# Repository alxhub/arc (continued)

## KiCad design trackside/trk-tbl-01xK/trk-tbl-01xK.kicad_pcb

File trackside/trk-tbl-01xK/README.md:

# ARC-TRK-TBL-01xK

ARC-TRK-TBL-01xK is the trackside controller for a Kato turntable. It connects to an ARC track hub over a LIN cable, moves the bridge, operates its lock, and counts the turntable's index contact as the bridge passes each stop. A homing sensor port can establish an absolute starting position.

The rails on the moving bridge receive power from a separate ARC district. This board passes that pair to the Kato cable and reports whether the feed is active. The controller does not drive the track rails.

An expansion port can host a nearby angle sensor or other I²C accessory.

[Board design](board.kdl)
[PCB layout](trk-tbl-01xK.kicad_pcb)

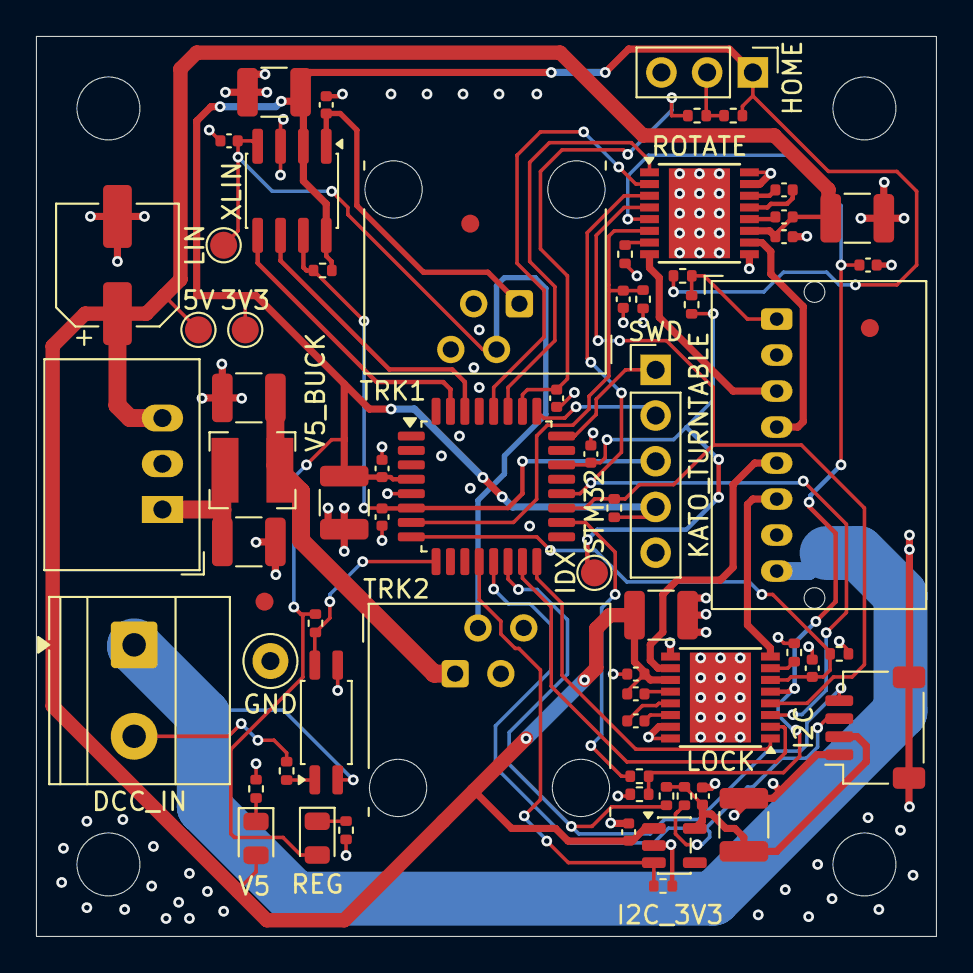
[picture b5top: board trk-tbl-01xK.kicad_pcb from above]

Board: 4 copper layers, 50.0 x 50.0 mm, 73 parts (0 on the bottom side), 48 nets.

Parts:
3V3, 5V: TestPoint; TestPoint_Pad_D1.5mm
C1, C6, C8, C12, C13, C16, C17, C21, C22: 100nF; C_0402_1005Metric
C2, C4, C5, C10, C11, C25: 10µF; C_1210_3225Metric
C3: 220pF; C_0402_1005Metric
C7: 4.7µF; C_1210_3225Metric
C9: 100µF; CP_Elec_6.3x5.8
C14, C15: 22nF; C_0402_1005Metric
C18, C23, C24: 1µF; C_0402_1005Metric
C19, C20: 10nF; C_0402_1005Metric
DCC_IN: Conn_01x02; TerminalBlock_Phoenix_MKDS-1,5-2-5.08_1x02_P5.08mm_Horizont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
FID1, FID2, FID3: Fiducial; Fiducial_1mm_Mask2mm
GND: TestPoint; TestPoint_Loop_D2.50mm_Drill1.0mm
H1, H2, H3, H4: MountingHole; MountingHole_3.5mm
HOME: Conn_01x03; PinHeader_1x03_P2.54mm_Vertical
I2C: Conn_01x04_MountingPin; JST_SH_SM04B-SRSS-TB_1x04-1MP_P1.00mm_Horizontal
I2C_3V3: AP2112K-3.3; SOT-23-5
IDX: TestPoint; TestPoint_Pad_D1.5mm
KATO_TURNTABLE: Conn_01x08; JST_PA_S08B-PASK-2_1x08_P2.00mm_Horizontal
L1: 15µH; L_Bourns-SRN4018
LIN: TestPoint; TestPoint_Pad_D1.5mm
LOCK: DRV8874PWPR; HTSSOP-16-1EP_4.4x5mm_P0.65mm_EP3.4x5mm
R1, R4, R5, R11: 10kΩ; R_0402_1005Metric
R2, R3: 20kΩ; R_0402_1005Metric
R6: 1MΩ; R_0402_1005Metric
R7, R8: 1.21kΩ; R_0402_1005Metric
R9: 2.2kΩ; R_0402_1005Metric
R10, R12: 1kΩ; R_0402_1005Metric
R13: 11kΩ; R_0402_1005Metric
R14, R17: 100kΩ; R_0402_1005Metric
R15: 680Ω; R_0402_1005Metric
R16: 1.5kΩ; R_0402_1005Metric
R18, R19: 4.7kΩ; R_0402_1005Metric
REG: green; LED_0805_2012Metric
ROTATE: DRV8874PWPR; HTSSOP-16-1EP_4.4x5mm_P0.65mm_EP3.4x5mm
STM32: STM32C092KBTx; LQFP-32_7x7mm_P0.8mm
SWD: Conn_01x05; PinHeader_1x05_P2.54mm_Vertical
TRK1, TRK2: RJ11; RJ11_Stewart_SS-90000-006_Horizontal
U1: FODM214; SOP-4_4.4x2.6mm_P1.27mm
V5: green; LED_0805_2012Metric
V5_BUCK: R-78E5.0-1.0; Converter_DCDC_RECOM_R-78E-0.5_THT
XLIN: NCV7428D13R2G; SOIC-8_3.9x4.9mm_P1.27mm

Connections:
unnamed: I2C_3V3.3, R17.1, STM32.12
unnamed: C15.1, LOCK.13
unnamed: C15.2, LOCK.14
unnamed: LOCK.7, R3.1
unnamed: C17.2, LOCK.12
unnamed: R15.1, REG.1
unnamed: C14.1, ROTATE.13
unnamed: C14.2, ROTATE.14
unnamed: R2.1, ROTATE.7
unnamed: C16.2, ROTATE.12
unnamed: R13.2, U1.1
unnamed: R16.1, V5.1
expansion/pulls/i2c.scl: I2C.4, R19.1, STM32.14
expansion/pulls/i2c.sda: I2C.3, R18.1, STM32.13
expansion/pulls/rail.rail: C24.1, C25.1, I2C.2, I2C_3V3.5, R18.2, R19.2
lin/rxd: STM32.31, XLIN.5
lin/txd: STM32.30, XLIN.6
node/GND: C1.2, C2.2, C3.2, C4.2, C5.2, C6.2, C7.2, C8.2, C9.2, C10.2, C11.2, C12.2, C13.2, C18.2, C19.2, C20.2, C21.2, C22.2, C23.2, C24.2, C25.2, GND.1, HOME.3, I2C.1, I2C.MP, I2C_3V3.2, KATO_TURNTABLE.2, LOCK.9, LOCK.15, LOCK.16, LOCK.17, R2.2, R3.2, R6.2, R7.2, R8.2, R15.2, R16.2, R17.2, ROTATE.9, ROTATE.15, ROTATE.16, ROTATE.17, STM32.5, SWD.5, TRK1.4, TRK2.4, U1.3, V5_BUCK.2, XLIN.3
node/LIN: C3.1, LIN.1, TRK1.2, TRK2.2, XLIN.4
node/V5: TRK1.3, TRK2.3
node/VPWR: C1.1, C4.1, L1.1, TRK1.1, TRK2.1, XLIN.1
node/v3v3.rail: 3V3.1, C2.1, C6.1, C7.1, HOME.1, R1.2, R4.2, R9.2, R11.2, R14.2, REG.2, STM32.4, SWD.4, XLIN.2, XLIN.8
nrst: C8.1, R1.1, STM32.6, SWD.3, XLIN.7
swd/swd.swclk: STM32.25, SWD.2
swd/swd.swdio: STM32.24, SWD.1
table/HOME: HOME.2, R11.1, R12.1
table/INDEX: KATO_TURNTABLE.1, R9.1, R10.1
table/TRK_A: DCC_IN.2, KATO_TURNTABLE.7, R13.1
table/TRK_B: DCC_IN.1, KATO_TURNTABLE.8, U1.2
table/VREF: C18.1, LOCK.5, R5.2, R6.1, ROTATE.5
table/VREF_PWM: R5.1, STM32.18
table/home: C22.1, R12.2, STM32.26
table/index: C21.1, IDX.1, R10.2, STM32.22
table/lock/A: KATO_TURNTABLE.5, LOCK.10
table/lock/B: KATO_TURNTABLE.6, LOCK.8
table/lock/EN: LOCK.1, STM32.16
table/lock/ISENSE: C20.1, LOCK.6, R8.1, STM32.8
table/lock/PH: LOCK.2, STM32.15
table/nFAULT: LOCK.4, R4.1, ROTATE.4, STM32.19
table/nSLEEP: LOCK.3, ROTATE.3, STM32.20
table/rotate/A: KATO_TURNTABLE.3, ROTATE.8
table/rotate/B: KATO_TURNTABLE.4, ROTATE.10
table/rotate/EN: ROTATE.1, STM32.27
table/rotate/ISENSE: C19.1, R7.1, ROTATE.6, STM32.7
table/rotate/PH: ROTATE.2, STM32.28
track/present: R14.1, STM32.9, U1.4
v5/filtered.rail: C5.1, L1.2, V5_BUCK.1
v5/out.rail: 5V.1, C9.1, C10.1, C11.1, C12.1, C13.1, C16.1, C17.1, C23.1, I2C_3V3.1, LOCK.11, ROTATE.11, V5.2, V5_BUCK.3

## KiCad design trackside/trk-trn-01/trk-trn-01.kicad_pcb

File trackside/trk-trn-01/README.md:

# ARC-TRK-TRN-01

ARC-TRK-TRN-01 is a trackside turnout controller. It connects to a LIN leg and operates four turnout machines, two on each terminal bank. A local energy store supplies the brief throw pulses so they do not pull that current through the leg cable.

The node measures the store before and after a throw, reports machine faults to the hub, and shows when it is ready to operate. A Qwiic port provides local expansion for trackside accessories.

[Board design](board.kdl)
[PCB layout](trk-trn-01.kicad_pcb)

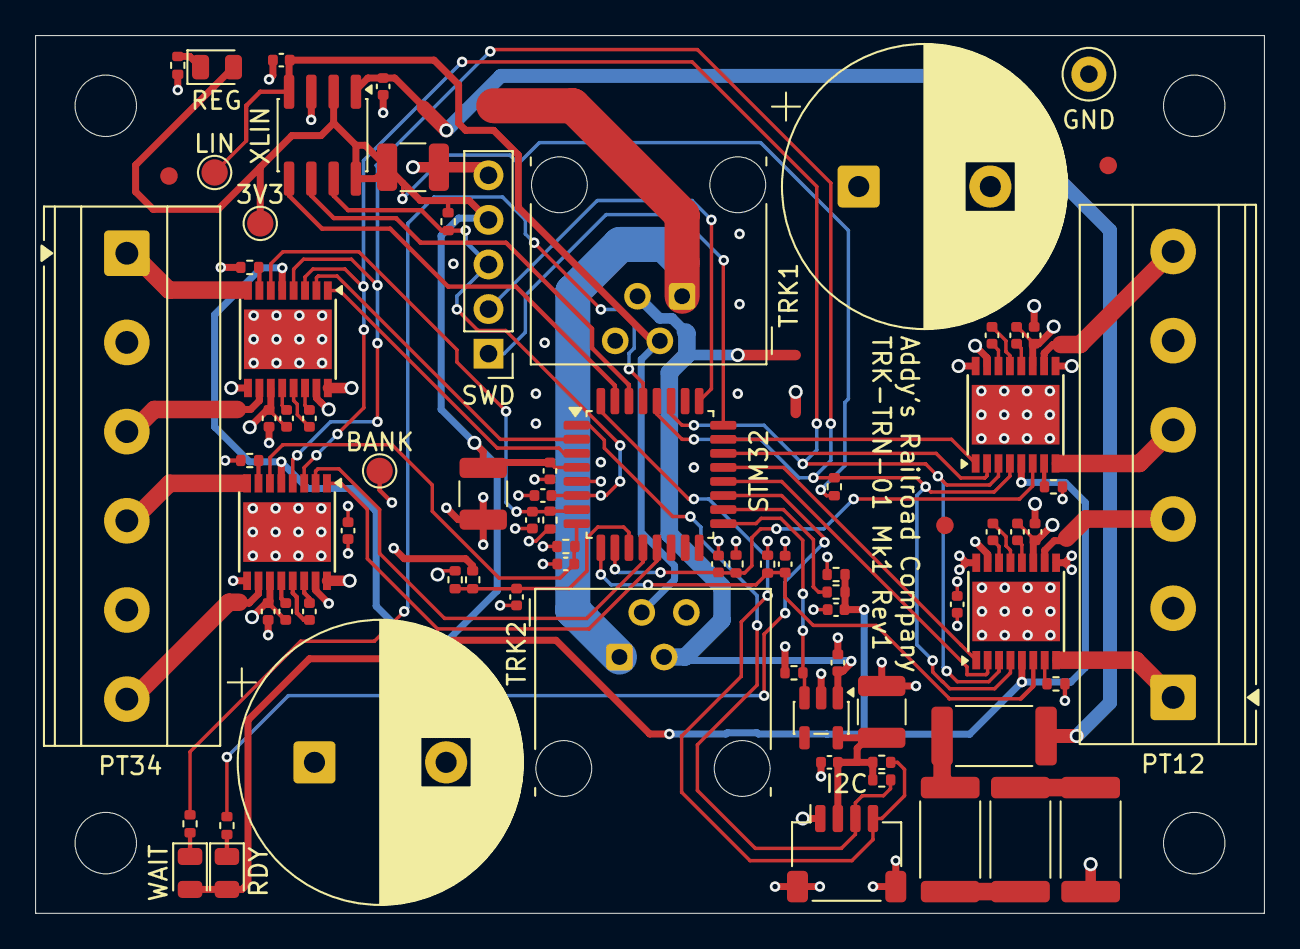
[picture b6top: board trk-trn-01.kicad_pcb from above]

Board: 4 copper layers, 70.0 x 50.0 mm, 82 parts (0 on the bottom side), 64 nets.

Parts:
3V3: TestPoint; TestPoint_Pad_D1.5mm
BANK: TestPoint; TestPoint_Pad_D1.5mm
C1, C6, C7, C8, C10, C12, C14, C16, C18, C20, C22, C24, C26, C28: 100nF; C_0402_1005Metric
C2, C31: 10µF; C_1210_3225Metric
C3: 220pF; C_0402_1005Metric
C4, C5: 3.3mF; CP_Radial_D16.0mm_P7.50mm
C9, C29, C30: 1µF; C_0402_1005Metric
C11, C15, C19, C23: 22nF; C_0402_1005Metric
C13, C17, C21, C25: 10nF; C_0402_1005Metric
C27: 4.7µF; C_1210_3225Metric
FID1, FID2, FID3: Fiducial; Fiducial_1mm_Mask2mm
GND: TestPoint; TestPoint_Loop_D2.50mm_Drill1.0mm
H1, H2, H3, H4: MountingHole; MountingHole_3.5mm
I2C: Conn_01x04_MountingPin; JST_SH_SM04B-SRSS-TB_1x04-1MP_P1.00mm_Horizontal
LIN: TestPoint; TestPoint_Pad_D1.5mm
PT12, PT34: Conn_01x06; TerminalBlock_Phoenix_MKDS-1,5-6-5.08_1x06_P5.08mm_Horizont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
R1, R8, R10: 10kΩ; R_0402_1005Metric
R2, R3, R4, R5: 24.9Ω; R_2512_6332Metric
R6, R22: 100kΩ; R_0402_1005Metric
R7: 18kΩ; R_0402_1005Metric
R9: 1MΩ; R_0402_1005Metric
R11, R13, R15, R17: 20kΩ; R_0402_1005Metric
R12, R14, R16, R18: 1.21kΩ; R_0402_1005Metric
R19: 680Ω; R_0402_1005Metric
R20, R21: 620Ω; R_0402_1005Metric
R23, R24: 4.7kΩ; R_0402_1005Metric
RDY: green; LED_0805_2012Metric
REG: green; LED_0805_2012Metric
STM32: STM32C092KBTx; LQFP-32_7x7mm_P0.8mm
SWD: Conn_01x05; PinHeader_1x05_P2.54mm_Vertical
TRK1, TRK2: RJ11; RJ11_Stewart_SS-90000-006_Horizontal
U1, U2, U3, U4: DRV8874PWPR; HTSSOP-16-1EP_4.4x5mm_P0.65mm_EP3.4x5mm
U5: AP2112K-3.3; SOT-23-5
WAIT: red; LED_0805_2012Metric
XLIN: NCV7428D13R2G; SOIC-8_3.9x4.9mm_P1.27mm

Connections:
unnamed: R2.2, R3.1
unnamed: R3.2, R4.1
unnamed: R4.2, R5.1
unnamed: R20.1, RDY.1
unnamed: R19.1, REG.1
unnamed: R20.2, STM32.19
unnamed: R21.2, STM32.29
unnamed: C11.1, U1.13
unnamed: C11.2, U1.14
unnamed: R11.1, U1.7
unnamed: C12.2, U1.12
unnamed: C15.1, U2.13
unnamed: C15.2, U2.14
unnamed: R13.1, U2.7
unnamed: C16.2, U2.12
unnamed: C19.1, U3.13
unnamed: C19.2, U3.14
unnamed: R15.1, U3.7
unnamed: C20.2, U3.12
unnamed: C23.1, U4.13
unnamed: C23.2, U4.14
unnamed: R17.1, U4.7
unnamed: C24.2, U4.12
unnamed: R21.1, WAIT.1
VREF_PWM: R8.1, STM32.18
bank/sense: C8.1, R6.2, R7.1, STM32.11
cdu/BANK: BANK.1, C4.1, C5.1, C6.1, C7.1, C10.1, C12.1, C14.1, C16.1, C18.1, C20.1, C22.1, C24.1, R5.2, R6.1, U1.11, U2.11, U3.11, U4.11
ch0/EN: STM32.21, U1.1
ch0/ISENSE: C13.1, R12.1, STM32.9, U1.6
ch0/PH: STM32.20, U1.2
ch1/EN: STM32.23, U2.1
ch1/ISENSE: C17.1, R14.1, STM32.10, U2.6
ch1/PH: STM32.22, U2.2
ch2/EN: STM32.3, U3.1
ch2/ISENSE: C21.1, R16.1, STM32.7, U3.6
ch2/PH: STM32.2, U3.2
ch3/EN: STM32.13, U4.1
ch3/ISENSE: C25.1, R18.1, STM32.8, U4.6
ch3/PH: STM32.12, U4.2
expansion/expansion/en: R22.1, STM32.17, U5.3
expansion/pulls/i2c.scl: I2C.4, R24.1, STM32.32
expansion/pulls/i2c.sda: I2C.3, R23.1, STM32.1
expansion/pulls/rail.rail: C30.1, C31.1, I2C.2, R23.2, R24.2, U5.5
lin/rxd: STM32.31, XLIN.5
lin/txd: STM32.30, XLIN.6
machines/a0: PT12.1, U1.8
machines/a1: PT12.4, U2.8
machines/a2: PT34.1, U3.8
machines/a3: PT34.4, U4.8
machines/b0: PT12.3, U1.10
machines/b1: PT12.6, U2.10
machines/b2: PT34.3, U3.10
machines/b3: PT34.6, U4.10
machines/vref: C9.1, R8.2, R9.1, U1.5, U2.5, U3.5, U4.5
nFAULT: R10.1, STM32.28, U1.4, U2.4, U3.4, U4.4
nSLEEP: STM32.27, U1.3, U2.3, U3.3, U4.3
node/GND: C1.2, C2.2, C3.2, C4.2, C5.2, C6.2, C7.2, C8.2, C9.2, C10.2, C13.2, C14.2, C17.2, C18.2, C21.2, C22.2, C25.2, C26.2, C27.2, C28.2, C29.2, C30.2, C31.2, GND.1, I2C.1, I2C.MP, PT12.2, PT12.5, PT34.2, PT34.5, R7.2, R9.2, R11.2, R12.2, R13.2, R14.2, R15.2, R16.2, R17.2, R18.2, R19.2, R22.2, STM32.5, SWD.5, TRK1.4, TRK2.4, U1.9, U1.15, U1.16, U1.17, U2.9, U2.15, U2.16, U2.17, U3.9, U3.15, U3.16, U3.17, U4.9, U4.15, U4.16, U4.17, U5.2, XLIN.3
node/LIN: C3.1, LIN.1, TRK1.2, TRK2.2, XLIN.4
node/V5: C29.1, TRK1.3, TRK2.3, U5.1
node/VPWR: C1.1, R2.1, TRK1.1, TRK2.1, XLIN.1
node/v3v3.rail: 3V3.1, C2.1, C26.1, C27.1, R1.2, R10.2, RDY.2, REG.2, STM32.4, SWD.4, WAIT.2, XLIN.2, XLIN.8
nrst: C28.1, R1.1, STM32.6, SWD.3, XLIN.7
swd/swd.swclk: STM32.25, SWD.2
swd/swd.swdio: STM32.24, SWD.1
